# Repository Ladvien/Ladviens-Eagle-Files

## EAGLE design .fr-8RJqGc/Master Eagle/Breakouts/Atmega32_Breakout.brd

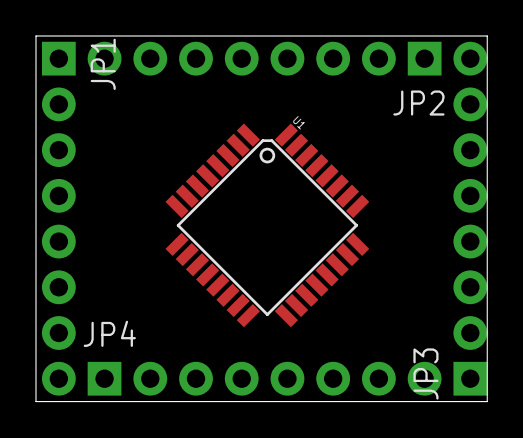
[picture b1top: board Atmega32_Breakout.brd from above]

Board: 2 copper layers, 25.1 x 20.3 mm, 5 parts (0 on the bottom side), 29 nets, no tracks yet.

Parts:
JP1, JP2, JP3, JP4: 1X08_PIN1_NO_SILK
U1: ATMEGA328P; TQFP32-08

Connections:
ADC6: JP3.8, U1.19
ADC7: JP2.1, U1.22
AGND: JP4.1, U1.21
AREF: JP4.4, U1.20
AVCC: JP4.7, U1.18
GND: JP1.8, U1.3, U1.5
PB0: JP1.2, U1.12
PB1: JP1.3, U1.13
PB2: JP1.4, U1.14
PB3: JP1.5, U1.15
PB4: JP1.6, U1.16
PB5: JP1.7, U1.17
PB6: JP4.3, U1.7
PB7: JP4.2, U1.8
PC0: JP3.2, U1.23
PC1: JP3.3, U1.24
PC2: JP3.4, U1.25
PC3: JP3.5, U1.26
PC4: JP3.6, U1.27
PC5: JP3.7, U1.28
PD0: JP2.2, U1.30
PD2: JP2.4, U1.32
PD3: JP2.5, U1.1
PD4: JP2.6, U1.2
PD5: JP2.7, U1.9
PD6: JP2.8, U1.10
PD7: JP1.1, U1.11
RES: JP4.8, U1.29
VCC: JP4.5, JP4.6, U1.4, U1.6

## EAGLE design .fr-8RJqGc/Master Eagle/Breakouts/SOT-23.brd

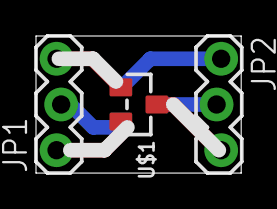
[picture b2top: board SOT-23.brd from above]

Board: 2 copper layers, 11.4 x 7.6 mm, 4 parts (1 on the bottom side), 6 nets.

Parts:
JP1, JP2: 1X03_LOCK
U$1, U$2: DMP1045U; SOT-23

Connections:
D: JP2.3, U$1.3
D2: JP2.2, U$2.3
G: JP1.3, U$1.1
G2: JP1.2, U$2.1
S: JP1.1, U$1.2
S2: JP2.1, U$2.2

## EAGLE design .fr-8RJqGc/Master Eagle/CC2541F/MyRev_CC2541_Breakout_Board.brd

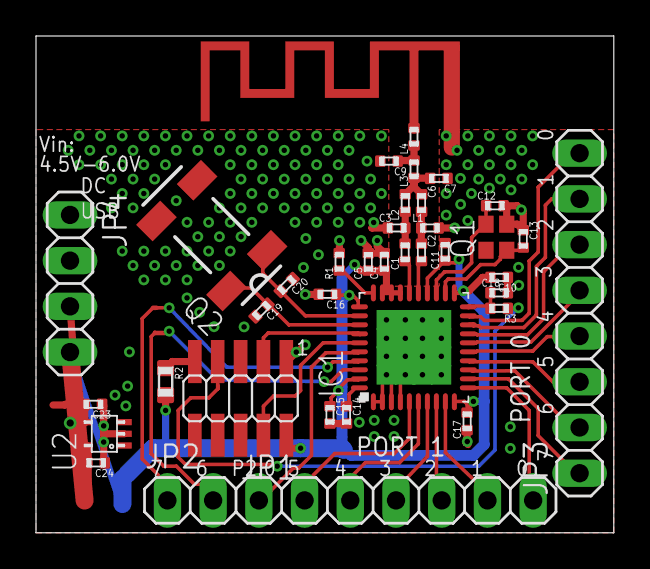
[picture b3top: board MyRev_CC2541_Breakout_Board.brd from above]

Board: 2 copper layers, 32.1 x 27.6 mm, 37 parts (0 on the bottom side), 38 nets.

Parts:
A1: TI_2.4GHZ_MIFALEFT; TI_2.4GHZ_MIFA_LEFT
C1, C2: 18p; C0402
C3, C6, C9: 1p; C0402
C4: 220p; C0402
C5, C10, C11, C16, C18, C23: 100n; C0402
C7: DNM; C0402
C12, C13: 12p; C0402
C14, C15: 1u; C0402
C17: C0402
C19, C20: 15p; C0402
C24: 470n; C0402
IC1: CC2540; QFN40-6X6
JP1: 2X05_1.27_SMD
JP2: 1X09
JP3: 1X08
JP4: 1X04
L1, L2: 2n; C0402
L3: 1n; C0402
L4: 3n; C0402
Q1: FA-128
Q2: MC-306
R1: 56k; C0402
R2: R0603; C0603
R3: 2.7k; C0402
U2: TPS71530; SC70

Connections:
GND: A1.GND, C3.1, C4.2, C5.2, C7.1, C9.2, C10.1, C11.2, C12.2, C13.1, C14.2, C15.2, C16.2, C17.1, C18.2, C19.2, C20.1, C23.1, C24.1, IC1.1, IC1.2, IC1.3, IC1.4, IC1.EXP@1, IC1.EXP@2, IC1.EXP@3, IC1.EXP@4, IC1.EXP@5, IC1.EXP@6, IC1.EXP@7, IC1.EXP@8, IC1.EXP@9, IC1.EXP@10, IC1.EXP@11, IC1.EXP@12, IC1.EXP@13, IC1.EXP@14, IC1.EXP@15, IC1.EXP@16, JP1.1, JP4.1, JP4.2, L1.2, Q1.2, Q1.4, R1.2, U2.2
unnamed: C1.1, IC1.26
unnamed: C2.2, IC1.25
unnamed: C1.2, C3.2, L2.1
unnamed: C2.1, C6.2, L1.1
unnamed: C6.1, C7.2, L2.2, L3.1
unnamed: C9.1, L3.2, L4.1
unnamed: IC1.30, R1.1
unnamed: C13.2, IC1.22, Q1.1
unnamed: C12.1, IC1.23, Q1.3
unnamed: C14.1, IC1.40
unnamed: JP1.7, R3.1
unnamed: JP1.9, R2.1
unnamed: IC1.34, JP1.3
unnamed: IC1.35, JP1.4
unnamed: C18.1, IC1.20, R3.2
unnamed: C20.2, IC1.32, Q2.1
unnamed: C19.1, IC1.33, Q2.4
unnamed: IC1.19, JP3.8
unnamed: IC1.18, JP3.7
unnamed: IC1.17, JP3.6
unnamed: IC1.16, JP3.5
unnamed: IC1.15, JP3.4
unnamed: IC1.14, JP3.3
unnamed: IC1.13, JP3.2
unnamed: IC1.12, JP3.1
unnamed: IC1.11, JP2.9
unnamed: IC1.9, JP2.8
unnamed: IC1.7, JP2.6
unnamed: IC1.8, JP2.7
unnamed: IC1.6, JP2.5
unnamed: IC1.38, JP2.2
unnamed: IC1.37, JP2.1
unnamed: C23.2, U2.4
unnamed: IC1.36, JP2.3
unnamed: IC1.5, JP2.4
unnamed: A1.FEED, L4.2
VDD: C4.1, C5.1, C10.2, C11.1, C15.1, C16.1, C17.2, C24.2, IC1.10, IC1.21, IC1.24, IC1.27, IC1.28, IC1.29, IC1.31, IC1.39, JP1.2, JP4.3, JP4.4, R2.2, U2.5

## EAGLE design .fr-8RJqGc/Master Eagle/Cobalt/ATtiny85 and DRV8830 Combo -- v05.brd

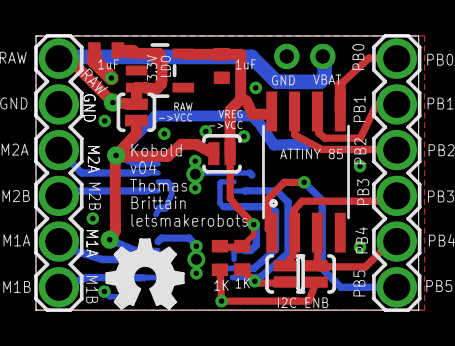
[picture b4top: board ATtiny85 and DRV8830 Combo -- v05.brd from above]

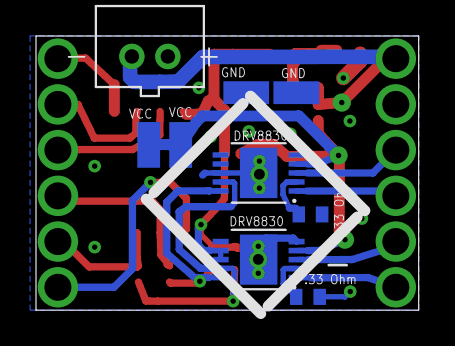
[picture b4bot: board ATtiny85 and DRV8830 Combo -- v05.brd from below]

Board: 2 copper layers, 21.3 x 15.2 mm, 22 parts (9 on the bottom side), 18 nets.

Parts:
1K: R3; R0402
C1, C2: 1uf; C0402
CN1: JST-PH-2-THM
PAD1, PAD2, PAD3, PAD4: SMD1,27-2,54
R1, R3: .33; R0402
R2: 1k; R0402
RAW: SOLDERJUMPERNO; SJ_2S-NO
SJ6, SJ7: SOLDERJUMPERNO; SJ_2S-NO
U1: V_REG_LDOSMD; SOT23-5
U2, U3: DRV8830; MSOP-10-GNDPAD
U$1, U$4: 1X6_SHORT_ROUND
U$2: ATTINY85; SO08-EIAJ
U$3: OSHW_FILLX150_NOTEXT
VREG: SOLDERJUMPERNO; SJ_2S-NO

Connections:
BAT_RAW: C1.1, CN1.2, RAW.1, U1.1, U1.3, U$4.1
GND: C1.2, C2.2, CN1.1, PAD1.1, PAD3.1, R1.1, R3.1, U1.2, U2.5, U2.GND, U3.5, U3.7, U3.8, U3.GND, U$2.4, U$4.2
M1_A: U2.3, U$4.5
M1_B: U2.1, U$4.6
M2_A: U3.3, U$4.3
M2_B: U3.1, U$4.4
unnamed: R1.2, U3.2
unnamed: R3.2, U2.2
PB0: U$1.1, U$2.5
PB1: U$1.2, U$2.6
PB2: U$1.3, U$2.7
PB3: SJ7.2, U$1.4, U$2.2
PB4: SJ6.2, U$1.5, U$2.3
PB5: U$1.6, U$2.1
SCL: R2.2, SJ7.1, U2.10, U3.10
SDA: 1K.2, SJ6.1, U2.9, U3.9
VCC: PAD2.1, PAD4.1, RAW.2, U2.4, U3.4, VREG.2
VREG: 1K.1, C2.1, R2.1, U1.5, U2.7, U2.8, U$2.8, VREG.1

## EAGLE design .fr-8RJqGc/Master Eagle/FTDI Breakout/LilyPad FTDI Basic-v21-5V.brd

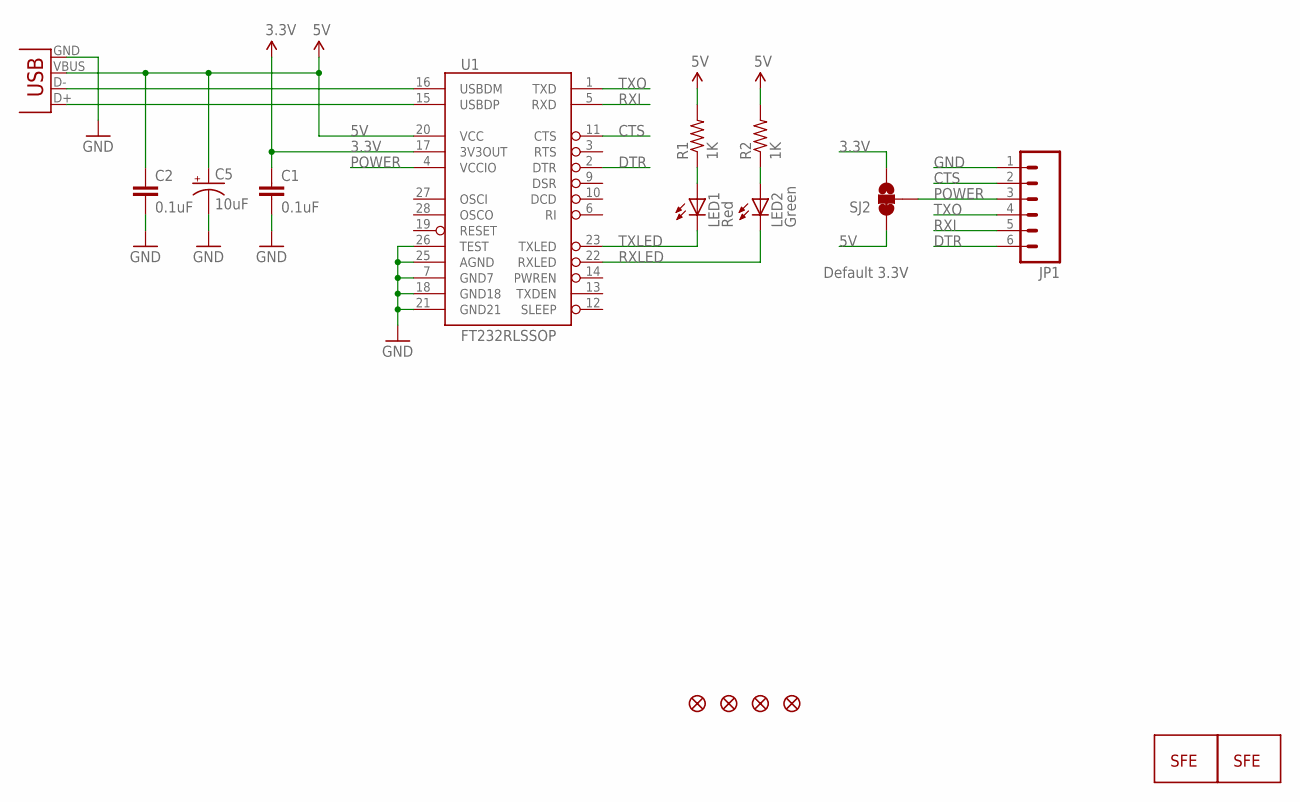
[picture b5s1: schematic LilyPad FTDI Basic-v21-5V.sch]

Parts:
C1, C2: 0.1uF; 0805
C5: 10uF; EIA3216
JP1: M06SMD-FEMALE-V2; 1X06-SMD-FEMALE-V2
JP2: LOGO-SFESK; SFE-LOGO-FLAME
JP7, JP8, JP9, JP10: FIDUCIAL1X2; FIDUCIAL-1X2
LED1: Red; LED-0603
LED2: Green; LED-0603
R1, R2: 1K; 0805
SJ2: SOLDERJUMPER_2WAYS; SJ_3
U1: FT232RLSSOP; SSOP28DB
U$2: LOGO-SFENW2; SFE-NEW-WEB
X2: USB-SMD-NS; USB-MINIB-NOSTOP

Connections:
3.3V: C1.1, SJ2.3, U1.17 (3V3OUT)
5V: C2.1, C5.A (+), R1.2, R2.2, SJ2.1, U1.20 (VCC), X2.VBUS
CTS: JP1.2, U1.11 (CTS)
DTR: JP1.6, U1.2 (DTR)
GND: C1.2, C2.2, C5.C (-), JP1.1, U1.7 (GND7), U1.18 (GND18), U1.21 (GND21), U1.25 (AGND), U1.26 (TEST), X2.GND
unnamed: LED1.A, R1.1
unnamed: LED2.A, R2.1
POWER: JP1.3, SJ2.2, U1.4 (VCCIO)
RXI: JP1.5, U1.5 (RXD)
RXLED: LED2.C, U1.22 (RXLED)
TXLED: LED1.C, U1.23 (TXLED)
TXO: JP1.4, U1.1 (TXD)
USB_D+: U1.15 (USBDP), X2.D+
USB_D-: U1.16 (USBDM), X2.D-

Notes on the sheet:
Default 3.3V

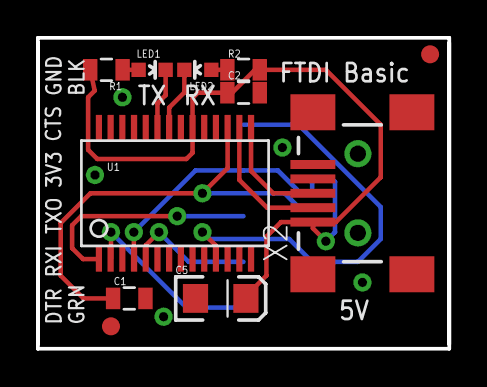
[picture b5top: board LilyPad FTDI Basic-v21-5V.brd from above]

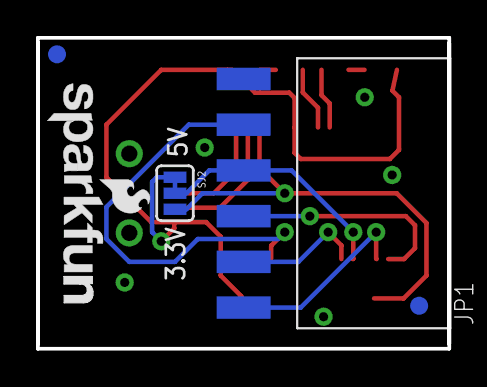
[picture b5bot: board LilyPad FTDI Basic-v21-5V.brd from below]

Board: 2 copper layers, 22.9 x 17.3 mm, 17 parts (6 on the bottom side), 14 nets.

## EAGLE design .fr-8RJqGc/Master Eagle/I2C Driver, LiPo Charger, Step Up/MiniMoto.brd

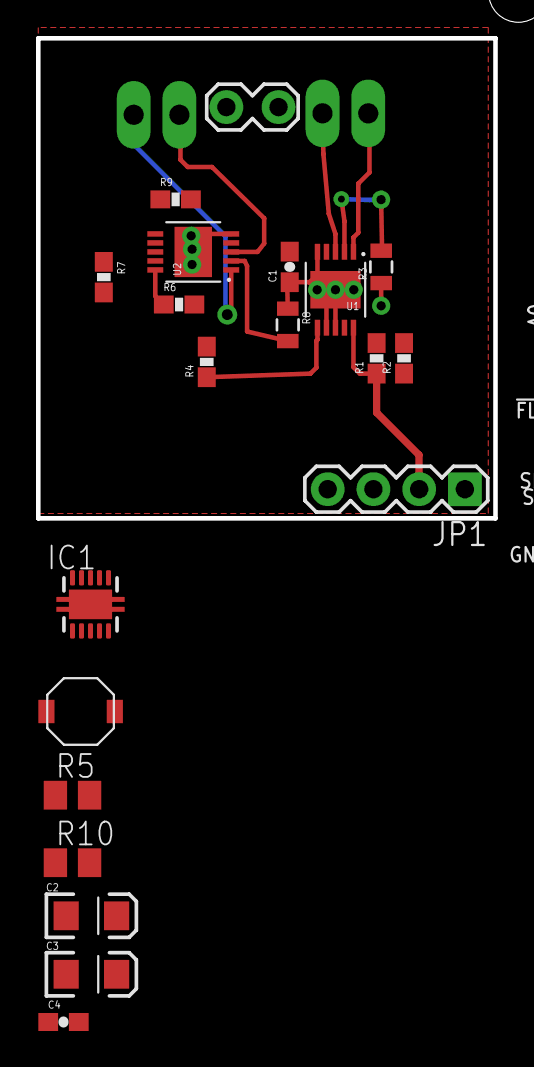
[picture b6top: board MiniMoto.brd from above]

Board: 2 copper layers, 25.4 x 26.7 mm, 26 parts (1 on the bottom side), 16 nets.

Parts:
2.2UH: VLF4012A
C1, C4: 0.1uF; 0603-CAP
C2, C3: EIA3216
IC1: TPS61200; S-PDSO-N10
J1, J5: M02PTH3; 1X02_LONGPADS
JP1: 1X04
JP3: 1X02_LOCK
LOGO2: OSHW-LOGOS; OSHW-LOGO-S
R1, R2, R6, R7: 1K; 0603-RES
R3, R8: 0.22; 0805
R4, R9: 10K; 0603-RES
R5, R10: M0805
STANDOFF1, STANDOFF2, STANDOFF3: STAND-OFF
U1, U2: DRV8830; MSOP-10-GNDPAD

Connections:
!FAULT: JP1.4, R4.1, R9.1, U1.6, U2.6
BAT+: 2.2UH.P$1, C2.A, IC1.5, IC1.6, IC1.7, IC1.8
GND: C1.1, C2.C, C3.C, C4.1, IC1.4, IC1.9, JP1.1, JP3.1, R3.1, R5.1, R8.1, U1.5, U1.7, U1.8, U1.GND, U2.5, U2.GND
unnamed: R8.2, U2.2
unnamed: R3.2, U1.2
unnamed: 2.2UH.P$2, IC1.3
unnamed: IC1.10, R5.2, R10.1
unnamed: C4.2, IC1.1
OUT1: J5.1, U1.3
OUT2: J5.2, U1.1
OUT3: J1.2, U2.3
OUT4: J1.1, U2.1
PP: IC1.PP, IC1.PP@1, IC1.PP@2
SCL: JP1.2, R1.1, R6.1, U1.10, U2.10
SDA: JP1.3, R2.1, R7.1, U1.9, U2.9
VCC: C1.2, C3.A, IC1.2, JP3.2, R1.2, R2.2, R4.2, R6.2, R7.2, R9.2, R10.2, U1.4, U2.4

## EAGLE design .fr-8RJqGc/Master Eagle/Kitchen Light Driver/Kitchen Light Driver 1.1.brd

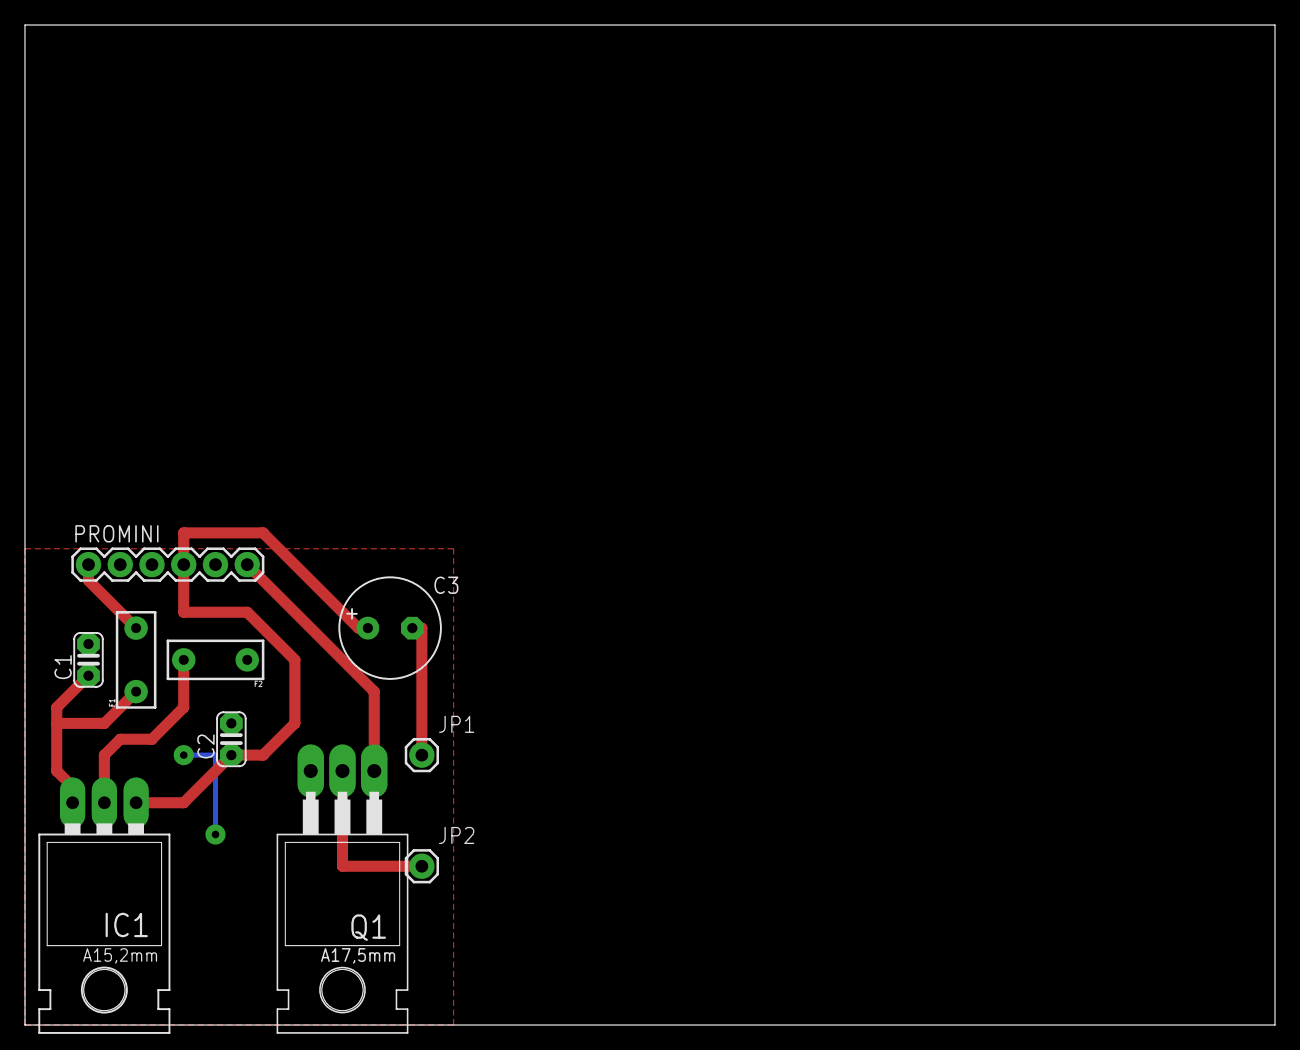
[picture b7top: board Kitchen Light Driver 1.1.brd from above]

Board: 2 copper layers, 100.0 x 80.0 mm, 10 parts (0 on the bottom side), 8 nets.

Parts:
C1, C2: C025-024X044
C3: E3,5-8
F1, F2: PTCPTH; PTC
IC1: 5v; 78XXL
JP1: To Leds; 1X01
JP2: From Leds; 1X01
PROMINI: 1X06
Q1: IRF540; TO220

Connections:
GND: C1.2, C2.2, F2.P$1, PROMINI.3, Q1.3
IRF540: PROMINI.6, Q1.1
unnamed: C1.1, F1.P$1, IC1.OUT
unnamed: F2.P$2, IC1.GND
unnamed: F1.P$2, PROMINI.1
unnamed: C3.-, JP1.1
unnamed: JP2.1, Q1.2
unnamed: C2.1, C3.+, IC1.IN, PROMINI.4

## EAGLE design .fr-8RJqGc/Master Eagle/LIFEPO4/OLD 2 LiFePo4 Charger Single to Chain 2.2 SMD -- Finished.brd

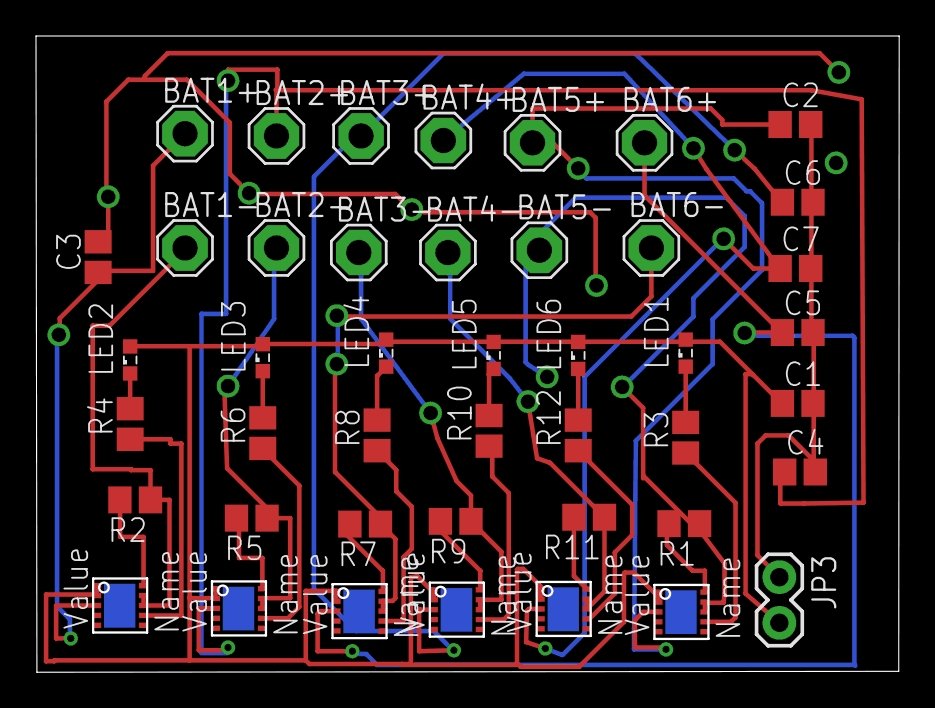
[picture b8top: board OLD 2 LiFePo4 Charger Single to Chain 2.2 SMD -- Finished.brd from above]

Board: 2 copper layers, 48.0 x 35.3 mm, 44 parts (0 on the bottom side), 32 nets.

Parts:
BAT1+, BAT1-, BAT2+, BAT2-, BAT3+, BAT3-, BAT4+, BAT4-, BAT5+, BAT5-, BAT6+, BAT6-: SE14
C1, C2, C3, C4, C5, C6, C7: 4.7; C0805
JP3: Vraw/Grnd; 1X02
LED1, LED2, LED3, LED4, LED5, LED6: 3.2v; SML0603
R1, R2, R5, R7, R9, R11: 1.5k; R0805
R3, R4, R6, R8, R10, R12: 1k; R0805
U$1, U$2, U$3, U$5, U$6, U$8: MCP73123/223

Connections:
GND: C1.2, C2.2, C3.2, C4.2, C5.2, C6.2, C7.2, JP3.1
unnamed: C1.1, JP3.2, LED1.A, LED2.A, LED3.A, LED4.A, LED5.A, LED6.A, U$1.1, U$1.2, U$2.1, U$2.2, U$3.1, U$3.2, U$5.1, U$5.2, U$6.1, U$6.2, U$8.1, U$8.2
unnamed: BAT5+.MP, C2.1, U$8.3
unnamed: R1.2, U$8.10
unnamed: BAT5-.MP, R1.1, U$8.8, U$8.9
unnamed: LED1.C, R3.2
unnamed: R3.1, U$8.7
unnamed: BAT1+.MP, C3.1, U$1.3
unnamed: BAT1-.MP, R2.1, U$1.8, U$1.9
unnamed: R4.1, U$1.7
unnamed: R2.2, U$1.10
unnamed: BAT2+.MP, C4.1, U$2.3
unnamed: LED2.C, R4.2
unnamed: BAT2-.MP, R5.1, U$2.8, U$2.9
unnamed: R6.1, U$2.7
unnamed: R5.2, U$2.10
unnamed: LED3.C, R6.2
unnamed: BAT6-.MP, R7.1, U$3.8, U$3.9
unnamed: R8.1, U$3.7
unnamed: R7.2, U$3.10
unnamed: LED4.C, R8.2
unnamed: BAT3+.MP, C6.1, U$5.3
unnamed: BAT3-.MP, R9.1, U$5.8, U$5.9
unnamed: R10.1, U$5.7
unnamed: R9.2, U$5.10
unnamed: LED5.C, R10.2
unnamed: BAT4+.MP, C7.1, U$6.3
unnamed: BAT4-.MP, R11.1, U$6.8, U$6.9
unnamed: R12.1, U$6.7
unnamed: R11.2, U$6.10
unnamed: LED6.C, R12.2
unnamed: BAT6+.MP, C5.1, U$3.3

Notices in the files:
parts and their libraries:
SparkFun-DigitalIC: Licensing: CC v3.0 Share-Alike You are welcome to use this library for commercial purposes.
SparkFun-Connectors: Licensing: Creative Commons ShareAlike 4.0 International - https://creativecommons.org/licenses/by-sa/4.0
